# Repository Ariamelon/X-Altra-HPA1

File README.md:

# X-Altra HPA-1
A compact high-power class A amplifier with a schematic from [this](https://www.diyaudio.com/community/threads/x-altra-hpa-1-class-a-headphone-amplifier.369499/) thread.
This design uses mostly SMT components with some THT. It is designed to fit in [this](https://item.taobao.com/item.htm?id=45818022688) case.

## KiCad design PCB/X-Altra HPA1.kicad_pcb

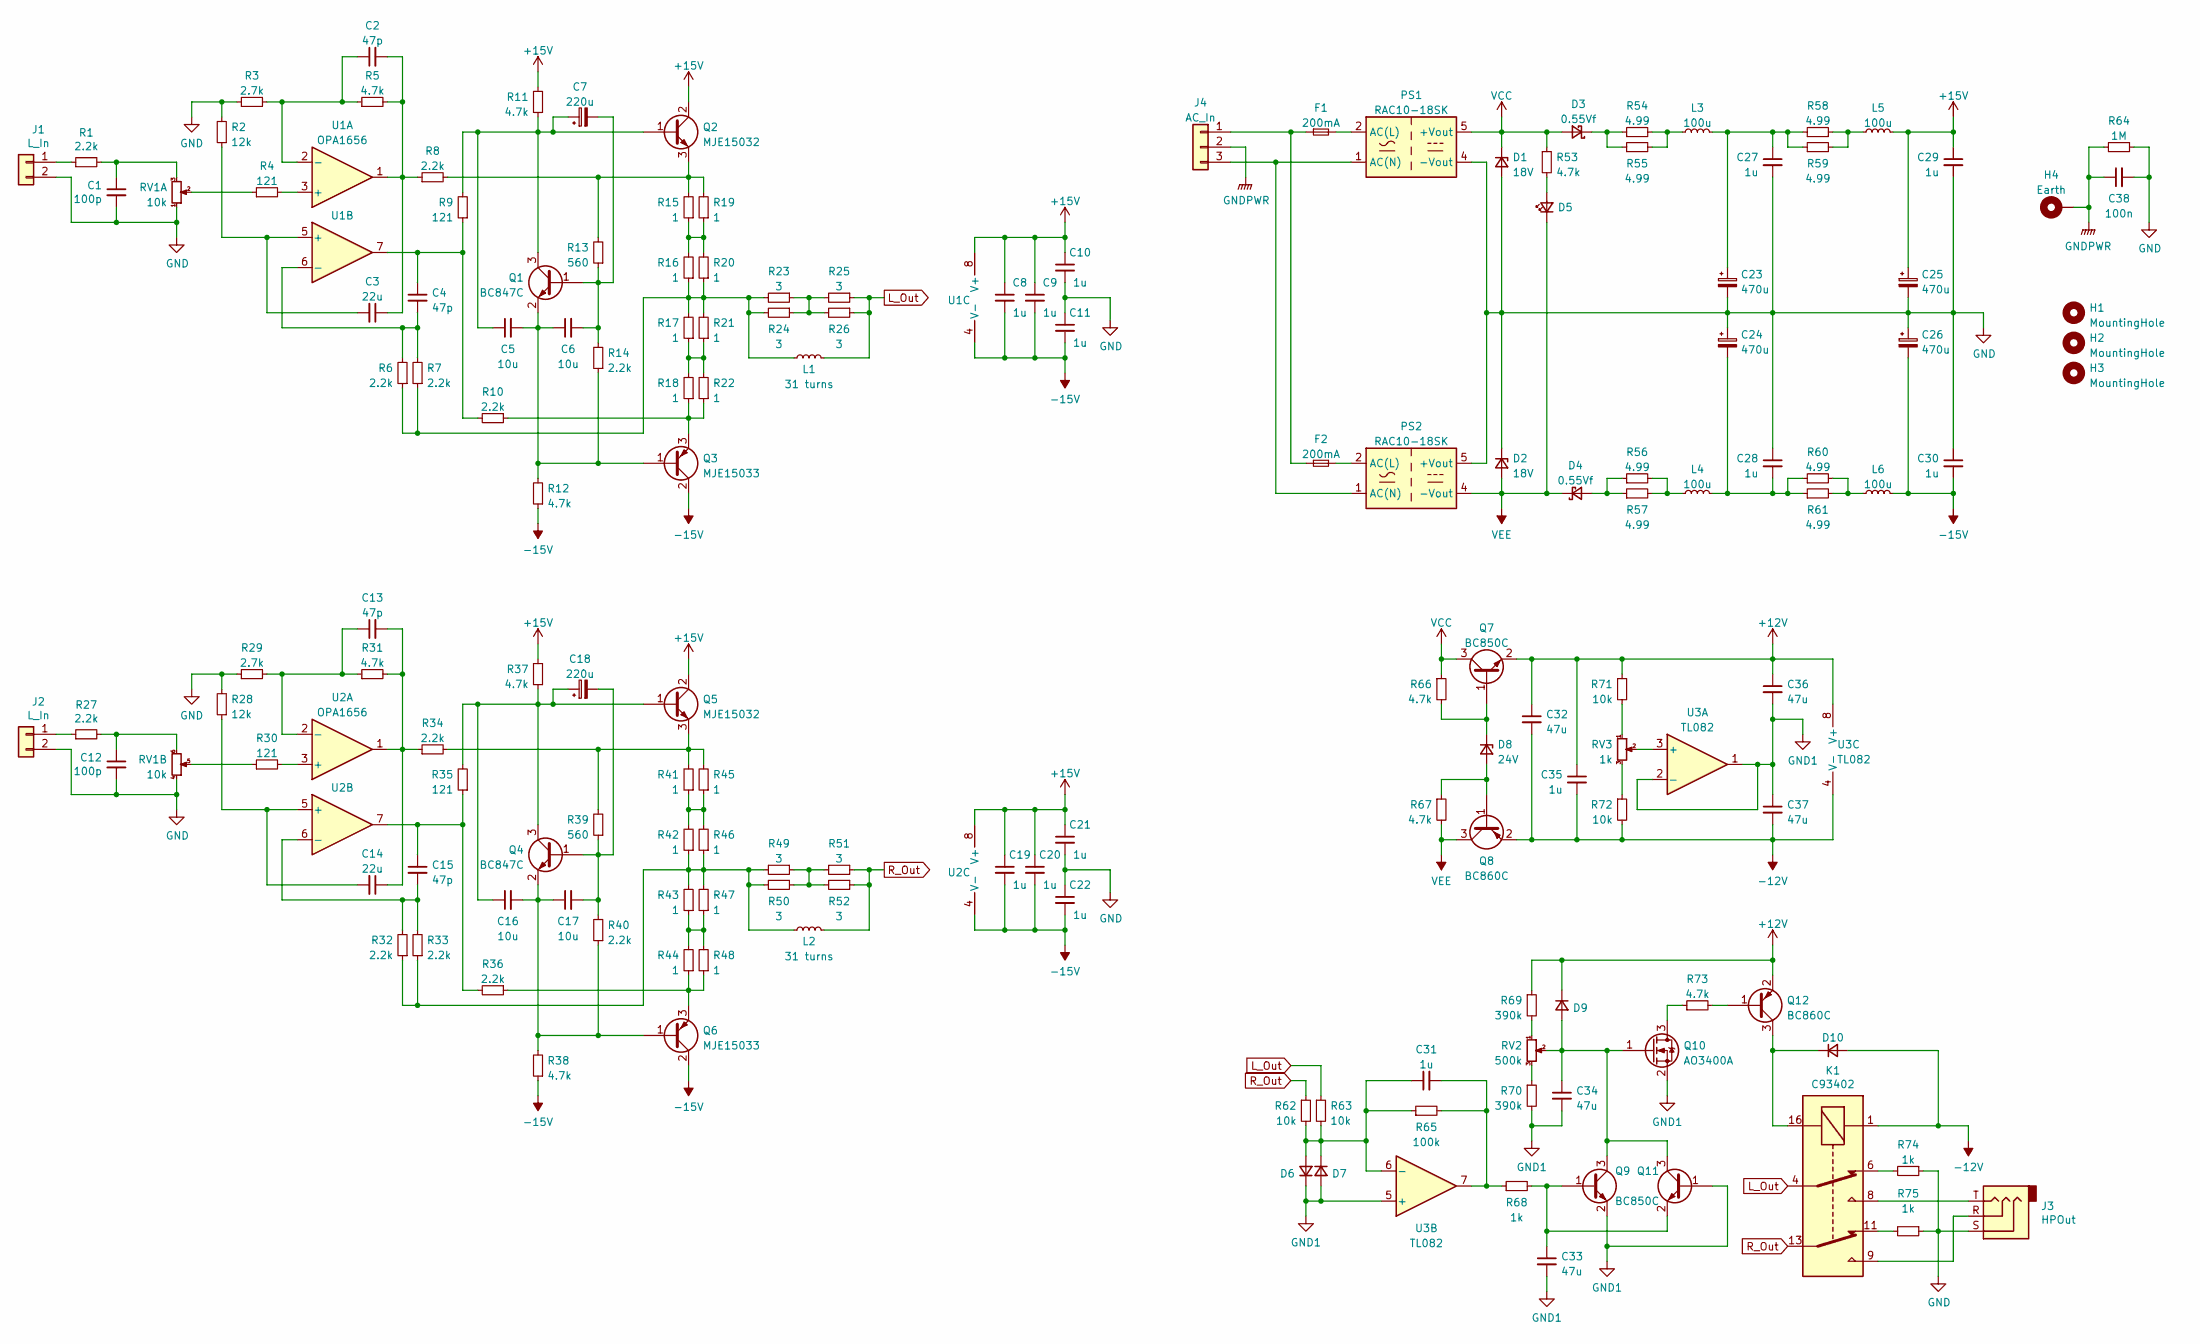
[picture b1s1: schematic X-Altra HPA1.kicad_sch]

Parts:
C1, C12: 100p; C_0603_1608Metric; Part number C1608NP01H101JT000N; LCSC part number C343033
C2, C4, C13, C15: 47p; C_0603_1608Metric; Part number C1608C0G1H470JT000N; LCSC part number C445755
C3, C14: 22u; C_Radial_D8.0mm_H11.5mm_P3.50mm; Part number UES1V220MPM1TA; LCSC part number N/A
C5, C6, C16, C17: 10u; C_0603_1608Metric; Part number CL10A106MA8NRNC; LCSC part number C2922482
C7, C18: 220u; CP_Elec_6.3x7.7; Part number EEEFK1C221XP; LCSC part number C128533
C8, C9, C10, C11, C19, C20, C21, C22, C27, C28, C29, C30, C31, C35: 1u; C_0603_1608Metric; Part number CL10A105KB8NNNC; LCSC part number C15849
C23, C24, C25, C26: 470u; CP_Elec_8x10.5; Part number EEEFT1E471GP; LCSC part number C193277
C32, C33, C34, C36, C37: 47u; C_1206_3216Metric; Part number C3216X5R1E476MTJ00E; LCSC part number C76659
C38: 100n; C_Rect_L26.5mm_W8.5mm_P22.50mm_MKS4; Part number PHE820ED6100MR06L2; LCSC part number C2926846
D1, D2: 18V; D_SMC; Part number SMCJ18CA-13-F; LCSC part number C135149
D3, D4: 0.55Vf; D_SMC; Part number B520C-13-F; LCSC part number C134460
D5: LED; LED_D3.0mm; Part number 204-10SUGC/S400-A5; LCSC part number C2927624
D6, D7, D9, D10: D; D_SOD-123; Part number 1N4148W; LCSC part number C81598
D8: 24V; D_SOD-123; Part number MM1Z5252B; LCSC part number C118720
F1, F2: 200mA; Fuseholder_Cylinder-5x20mm_Schurter_0031_8201_Horizontal_Op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; Part number 0031.8201; LCSC part number C58066
H1, H2, H3: MountingHole; MountingHole_4.3mm_M4
H4: Earth; MountingHole_4.3mm_M4_Pad
J1, J2: L_In; JST_XH_B2B-XH-A_1x02_P2.50mm_Vertical
J3: HPOut; Jack_6.35mm_Neutrik_NMJ6HCD2_Horizontal; Part number NMJ6HCD2; LCSC part number C368502
J4: AC_In; JST_VH_B3P-VH_1x03_P3.96mm_Vertical; Part number B3P-VH(LF)(SN); LCSC part number C160316
K1: C93402; Relay_DPDT_Omron_G5V-2; Part number C93402; LCSC part number C128021
L1, L2: 31 turns; L_Toroid_D15mm_W4mm; Part number N/A; LCSC part number N/A
L3, L4, L5, L6: 100u; L_TDK_SLF7032; Part number SPM7054VT-101M-D; LCSC part number C2045491
PS1, PS2: RAC10-18SK; Converter_ACDC_Recom_RAC20-xxSK_THT; Part number RAC10-18SK; LCSC part number N/A
Q1, Q4: BC847C; SOT-23; Part number BC847C,215; LCSC part number C8664
Q2, Q5: MJE15032; TO-220-3_Vertical; Part number MJE15032G; LCSC part number C134071
Q3, Q6: MJE15033; TO-220-3_Vertical; Part number MJE15033G; LCSC part number C134072
Q7, Q9, Q11: BC850C; SOT-23; Part number BC850C,215; LCSC part number C80071
Q8, Q12: BC860C; SOT-23; Part number BC860C,215; LCSC part number C454976
Q10: AO3400A; SOT-23; Part number AO3400A; LCSC part number C20917
R1, R6, R7, R8, R10, R14, R27, R32, R33, R34, R36, R40: 2.2k; R_1206_3216Metric; Part number RT1206BRD072K2L
R2, R28: 12k; R_1206_3216Metric; Part number RT1206FRE0712KL
R3, R29: 2.7k; R_1206_3216Metric; Part number RT1206BRD072K7L; LCSC part number C870633
R4, R9, R30, R35: 121; R_1206_3216Metric; Part number RT1206DRD07121RL; LCSC part number C136881
R5, R11, R12, R31, R37, R38, R53, R66, R67, R73: 4.7k; R_1206_3216Metric; Part number RT1206DRD074K7L
R13, R39: 560; R_1206_3216Metric; Part number RT1206BRD07560RL
R15, R16, R17, R18, R19, R20, R21, R22, R41, R42, R43, R44, R45, R46, R47, R48: 1; R_1206_3216Metric; Part number RT1206BRD071RL; LCSC part number C513714
R23, R24, R25, R26, R49, R50, R51, R52: 3; R_1206_3216Metric; Part number RT1206FRD073RL; LCSC part number C326707
R54, R55, R56, R57, R58, R59, R60, R61: 4.99; R_1206_3216Metric; Part number RT1206BRD074R99L; LCSC part number C326584
R62, R63, R71, R72: 10k; R_1206_3216Metric; Part number RT1206FRD0710KL; LCSC part number C705072
R64: 1M; R_1206_3216Metric; Part number RT1206FRE071ML; LCSC part number C375528
R65: 100k; R_1206_3216Metric; Part number RT1206FRD07100KL; LCSC part number C326828
R68, R74, R75: 1k; R_1206_3216Metric; Part number RT1206BRD071KL; LCSC part number C706405
R69, R70: 390k; R_1206_3216Metric; Part number RT1206BRD07392KL
RV1: 10k; ALPS_RK27112; Part number RK27112A00AK; LCSC part number C470507
RV2: 500k; Potentiometer_Vishay_T73YP_Vertical; Part number 3362P-1-504; LCSC part number C125021
RV3: 1k; Potentiometer_Bourns_3266W_Vertical; Part number 3266W-1-102; LCSC part number C123431
U1, U2: OPA1656; SOIC-8_3.9x4.9mm_P1.27mm; Part number OPA1656IDR; LCSC part number C1849431
U3: TL082; SOIC-8_3.9x4.9mm_P1.27mm; Part number TL082BCDT; LCSC part number C190361

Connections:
+12V: C32.1, C35.1, C36.1, D9.1 (K), Q7.2 (E), Q12.2 (E), R69.1, R71.1, U3.8 (V+)
+15V: C8.1, C9.1, C10.1, C19.1, C20.1, C21.1, C25.1, C29.1, L5.2, Q2.2 (C), Q5.2 (C), R11.2, R37.2, U1.8 (V+), U2.8 (V+)
-12V: C32.2, C35.2, C37.2, D10.2 (A), K1.1, Q8.2 (E), R72.2, U3.4 (V-)
-15V: C8.2, C9.2, C11.2, C19.2, C20.2, C22.2, C26.2, C30.2, L6.1, Q3.2 (C), Q6.2 (C), R12.1, R38.1, U1.4 (V-), U2.4 (V-)
GND: C1.2, C10.2, C11.1, C12.2, C21.2, C22.1, C23.2, C24.1, C25.2, C26.1, C27.2, C28.1, C29.2, C30.1, C38.2, D1.2 (A), D2.1 (K), J1.2, J2.2, J3.S, PS1.4 (-Vout), PS2.5 (+Vout), R2.2, R3.1, R28.2, R29.1, R64.1, R74.1, R75.1, RV1.1, RV1.4
GND1: C33.2, C34.2, C36.2, C37.1, D6.1 (K), D7.2 (A), Q9.2 (E), Q10.2 (S), Q11.1 (B), R70.2, U3.1, U3.2 (-), U3.5 (+)
GNDPWR: C38.1, H4.1, J4.2, R64.2
L_Out: K1.4, L1.2, R25.1, R26.1, R63.1
unnamed: C1.1, R1.2, RV1.3
unnamed: C2.1, R3.2, R5.1, U1.2 (-)
unnamed: C2.2, C3.1, R5.2, R8.1, U1.1
unnamed: C3.2, R2.1, U1.5 (+)
unnamed: C4.1, R9.1, R10.2, U1.7
unnamed: C4.2, R6.2, R7.2, U1.6 (-)
unnamed: C5.1, C7.1, Q1.3 (C), Q2.1 (B), R9.2, R11.1
unnamed: C5.2, C6.1, Q1.2 (E), Q3.1 (B), R12.2, R14.1
unnamed: C6.2, C7.2, Q1.1 (B), R13.1, R14.2
unnamed: C12.1, R27.2, RV1.6
unnamed: C13.1, R29.2, R31.1, U2.2 (-)
unnamed: C13.2, C14.1, R31.2, R34.1, U2.1
unnamed: C14.2, R28.1, U2.5 (+)
unnamed: C15.1, R35.1, R36.2, U2.7
unnamed: C15.2, R32.2, R33.2, U2.6 (-)
unnamed: C16.1, C18.1, Q4.3 (C), Q5.1 (B), R35.2, R37.1
unnamed: C16.2, C17.1, Q4.2 (E), Q6.1 (B), R38.2, R40.1
unnamed: C17.2, C18.2, Q4.1 (B), R39.1, R40.2
unnamed: C23.1, C27.1, L3.2, R58.1, R59.1
unnamed: C24.2, C28.2, L4.1, R60.1, R61.1
unnamed: C31.1, D6.2 (A), D7.1 (K), R62.2, R63.2, R65.1, U3.6 (-)
unnamed: C31.2, R65.2, R68.1, U3.7
unnamed: C33.1, Q9.1 (B), Q11.2 (E), R68.2
unnamed: C34.1, D9.2 (A), Q9.3 (C), Q10.1 (G), Q11.3 (C), RV2.2
unnamed: D3.1 (K), R54.1, R55.1
unnamed: D4.2 (A), R56.1, R57.1
unnamed: D5.2 (A), R53.2
unnamed: D8.1 (K), Q7.1 (B), R66.2
unnamed: D8.2 (A), Q8.1 (B), R67.1
unnamed: D10.1 (K), K1.16, Q12.3 (C)
unnamed: F1.1, F2.1, J4.1
unnamed: F1.2, PS1.2 (AC(L))
unnamed: F2.2, PS2.2 (AC(L))
unnamed: J1.1, R1.1
unnamed: J2.1, R27.1
unnamed: J3.R, K1.9
unnamed: J3.T, K1.8
unnamed: J4.3, PS1.1 (AC(N)), PS2.1 (AC(N))
unnamed: K1.6, R74.2
unnamed: K1.11, R75.2
unnamed: L1.1, R6.1, R7.1, R16.1, R17.2, R20.1, R21.2, R23.2, R24.2
unnamed: L2.1, R32.1, R33.1, R42.1, R43.2, R46.1, R47.2, R49.2, R50.2
unnamed: L3.1, R54.2, R55.2
unnamed: L4.2, R56.2, R57.2
unnamed: L5.1, R58.2, R59.2
unnamed: L6.2, R60.2, R61.2
unnamed: Q2.3 (E), R8.2, R13.2, R15.2, R19.2
unnamed: Q3.3 (E), R10.1, R18.1, R22.1
unnamed: Q5.3 (E), R34.2, R39.2, R41.2, R45.2
unnamed: Q6.3 (E), R36.1, R44.1, R48.1
unnamed: Q10.3 (D), R73.1
unnamed: Q12.1 (B), R73.2
unnamed: R4.1, RV1.2
unnamed: R4.2, U1.3 (+)
unnamed: R15.1, R16.2, R19.1, R20.2
unnamed: R17.1, R18.2, R21.1, R22.2
unnamed: R23.1, R24.1, R25.2, R26.2
unnamed: R30.1, RV1.5
unnamed: R30.2, U2.3 (+)
unnamed: R41.1, R42.2, R45.1, R46.2
unnamed: R43.1, R44.2, R47.1, R48.2
unnamed: R49.1, R50.1, R51.2, R52.2
unnamed: R69.2, RV2.1
unnamed: R70.1, RV2.3
unnamed: R71.2, RV3.1
unnamed: R72.1, RV3.3
unnamed: RV3.2, U3.3 (+)
R_Out: K1.13, L2.2, R51.1, R52.1, R62.1
VCC: D1.1 (K), D3.2 (A), PS1.5 (+Vout), Q7.3 (C), R53.1, R66.1
VEE: D2.2 (A), D4.1 (K), D5.1 (K), PS2.4 (-Vout), Q8.3 (C), R67.2

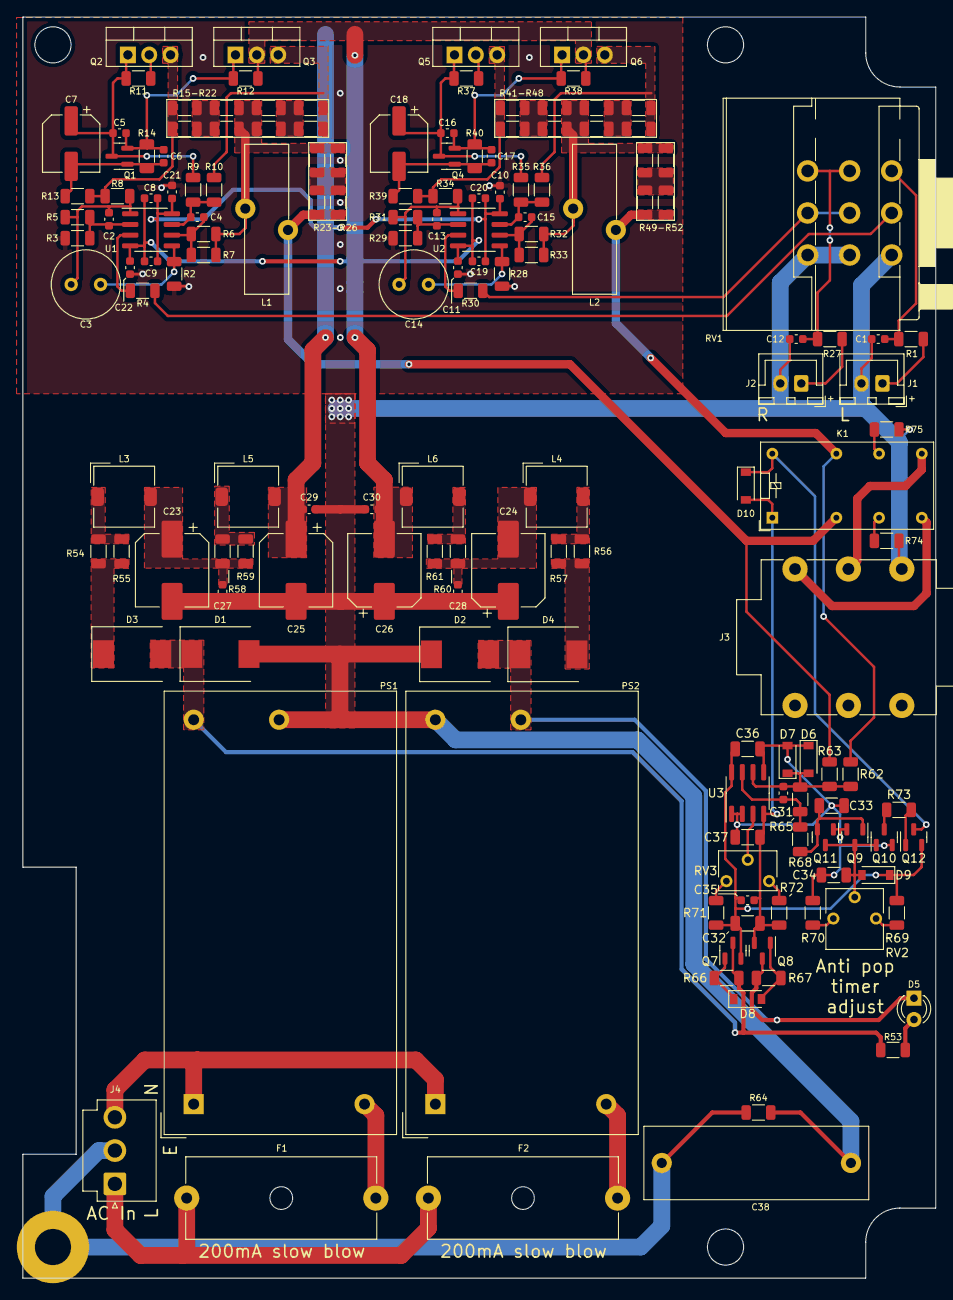
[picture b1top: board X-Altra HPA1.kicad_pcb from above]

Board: 2 copper layers, 108.6 x 150.0 mm, 160 parts (0 on the bottom side), 78 nets.

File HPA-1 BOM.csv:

Qty,Reference(s),Value,LCSC part number,Part number
2,"C1, C12",100p,C343033,C1608NP01H101JT000N
4,"C2, C4, C13, C15",47p,C445755,C1608C0G1H470JT000N
2,"C3, C14",22u,N/A,UES1V220MPM1TA
4,"C5, C6, C16, C17",10u,C2922482,CL10A106MA8NRNC
2,"C7, C18",220u,C128533,EEEFK1C221XP
14,"C8, C9, C10, C11, C19, C20, C21, C22, C27, C28, C29, C30, C31, C35",1u,C15849,CL10A105KB8NNNC
4,"C23, C24, C25, C26",470u,C193277,EEEFT1E471GP
5,"C32, C33, C34, C36, C37",47u,C76659,C3216X5R1E476MTJ00E
1,C38,100n,C2926846,PHE820ED6100MR06L2
2,"D1, D2",18V,C135149,SMCJ18CA-13-F
2,"D3, D4",0.55Vf,C134460,B520C-13-F
1,D5,LED,C2927624,204-10SUGC/S400-A5
4,"D6, D7, D9, D10",D,C81598,1N4148W
1,D8,24V,C118720,MM1Z5252B
2,"F1, F2",200mA,C58066,31.8201
1,J3,HPOut,C368502,NMJ6HCD2
1,J4,AC_In,C160316,B3P-VH(LF)(SN)
1,K1,C93402,C128021,C93402
4,"L3, L4, L5, L6",100u,C2045491,SPM7054VT-101M-D
2,"PS1, PS2",RAC10-18SK,N/A,RAC10-18SK
2,"Q1, Q4",BC847C,C8664,"BC847C,215"
3,"Q7, Q9, Q11",BC850C,C80071,"BC850C,215"
2,"Q2, Q5",KTC4370A,C125308,KTC4370A-Y-U/PF
2,"Q3, Q6",KTA1659A,C69800,KTA1659A-Y-U/PF
2,"Q8, Q12",BC860C,C454976,"BC860C,215"
1,Q10,AO3400A,C20917,AO3400A
12,"R1, R6, R7, R8, R10, R14, R27, R32, R33, R34, R36, R40",2.2k,,RT1206BRD072K2L
2,"R2, R28",12k,,RT1206FRE0712KL
2,"R3, R29",2.7k,C870633,RT1206BRD072K7L
4,"R4, R9, R30, R35",121,C136881,RT1206DRD07121RL
10,"R5, R11, R12, R31, R37, R38, R53, R66, R67, R73",4.7k,,RT1206DRD074K7L
2,"R13, R39",560,,RT1206BRD07560RL
16,"R15, R16, R17, R18, R19, R20, R21, R22, R41, R42, R43, R44, R45, R46, R47, R48",1,C513714,RT1206BRD071RL
8,"R23, R24, R25, R26, R49, R50, R51, R52",3,C326707,RT1206FRD073RL
8,"R54, R55, R56, R57, R58, R59, R60, R61",4.99,C326584,RT1206BRD074R99L
4,"R62, R63, R71, R72",10k,C705072,RT1206FRD0710KL
1,R64,1M,C375528,RT1206FRE071ML
1,R65,100k,C326828,RT1206FRD07100KL
3,"R68, R74, R75",1k,C706405,RT1206BRD071KL
2,"R69, R70",392k,,RT1206BRD07392KL
1,RV1,10k,C470507,RK27112A00AK
1,RV2,500k,C125021,3362P-1-504
1,RV3,1k,C123431,3266W-1-102
2,"U1, U2",OPA1656,C1849431,OPA1656IDR
1,U3,TL082,C190361,TL082BCDT

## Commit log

2022-06-13 Updated resistors to 1206 for less distortion
2022-06-13 Updated BOM
2022-06-15 Fixed error with silkscreen and LED routing
